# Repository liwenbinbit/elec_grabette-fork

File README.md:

# "Grabette"/"Gripette" Electronic Boards

This repository is part of the ["Grabette" project](https://github.com/pollen-robotics/grabette). It gathers several small PCBs of Grabette/Gripette. 

## Grabette
Grapette is the data acquisition side.

It is based on a battery-powered Raspberry PI 4 plus a [HAT](https://github.com/pollen-robotics/elec_RPI_Robot_HAT) to which a serie of sensing elements is added. Camera, Stereo Camera, angle sensors, IMU (included on the HAT) and a button + a LED as user interface.

 - angle_sensor

 - IMU (Not used)

 - HMI

## Gripette
Gripette is the actuator side. 

It also gathers data with the same Camera/Stereo Camera system and drive motors. The "under-HAT" electronic board is associated to a Raspberry PI zero 2W. It has a interface to the motors (now Feetech wiring). A Bulk-head board makes the mechanical interface with the arm that holds Gripette.

Bulk-head:

## Basically
 - Designed with KiCAD 9.

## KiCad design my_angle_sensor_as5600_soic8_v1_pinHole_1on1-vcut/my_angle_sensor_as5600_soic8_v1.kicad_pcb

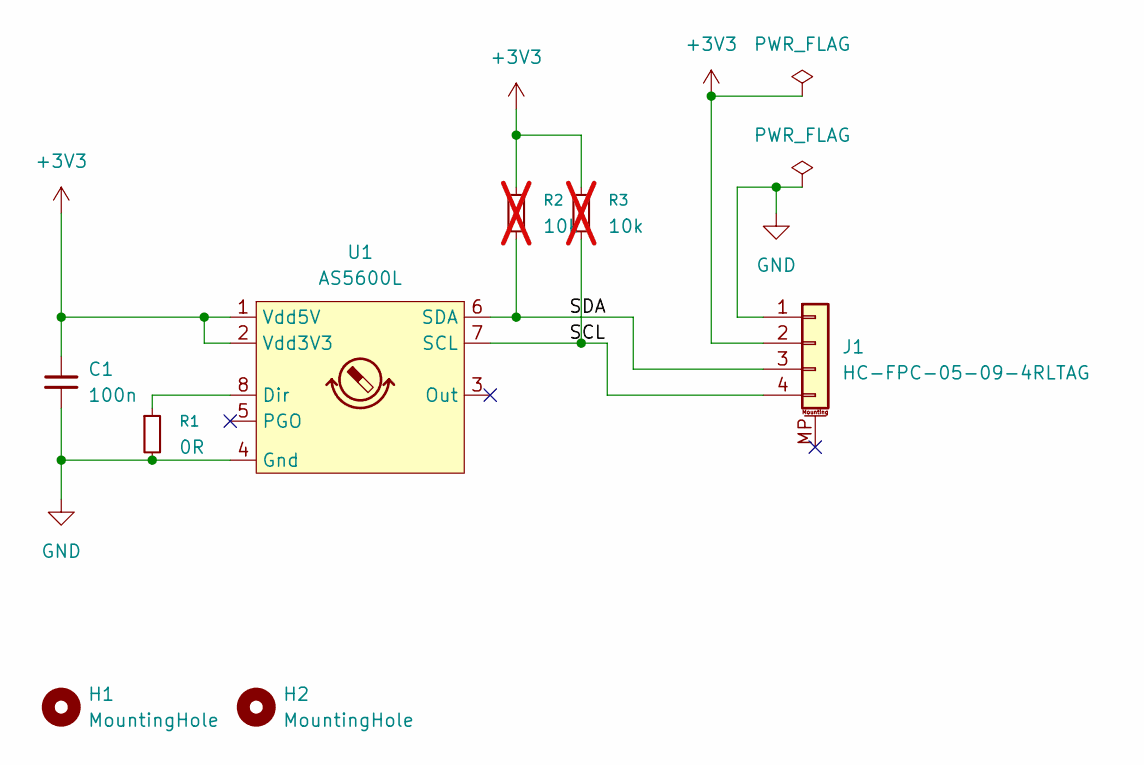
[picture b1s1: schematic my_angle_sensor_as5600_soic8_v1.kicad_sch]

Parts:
C1: 100n; C_0402_1005Metric; LCSC Part C307331
H1, H2: MountingHole; LocatingHole_NPTH_D1.0
J1: HC-FPC-05-09-4RLTAG; FPC-SMD_4P-P0.50_HC-FPC-05-09-4RLTAG; LCSC Part C5213746
R1: 0R; R_0402_1005Metric; LCSC Part C17168
R2, R3: 10k; R_0402_1005Metric; not fitted
U1: AS5600L; SOIC-8_3.9x4.9mm_P1.27mm; LCSC Part C2153666

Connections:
+3V3: C1.1, J1.2, R2.1, R3.1, U1.1 (Vdd5V), U1.2 (Vdd3V3)
/SCL: J1.4, R3.2, U1.7 (SCL)
/SDA: J1.3, R2.2, U1.6 (SDA)
GND: C1.2, J1.1, R1.2, U1.4 (Gnd)
unnamed: R1.1, U1.8 (Dir)

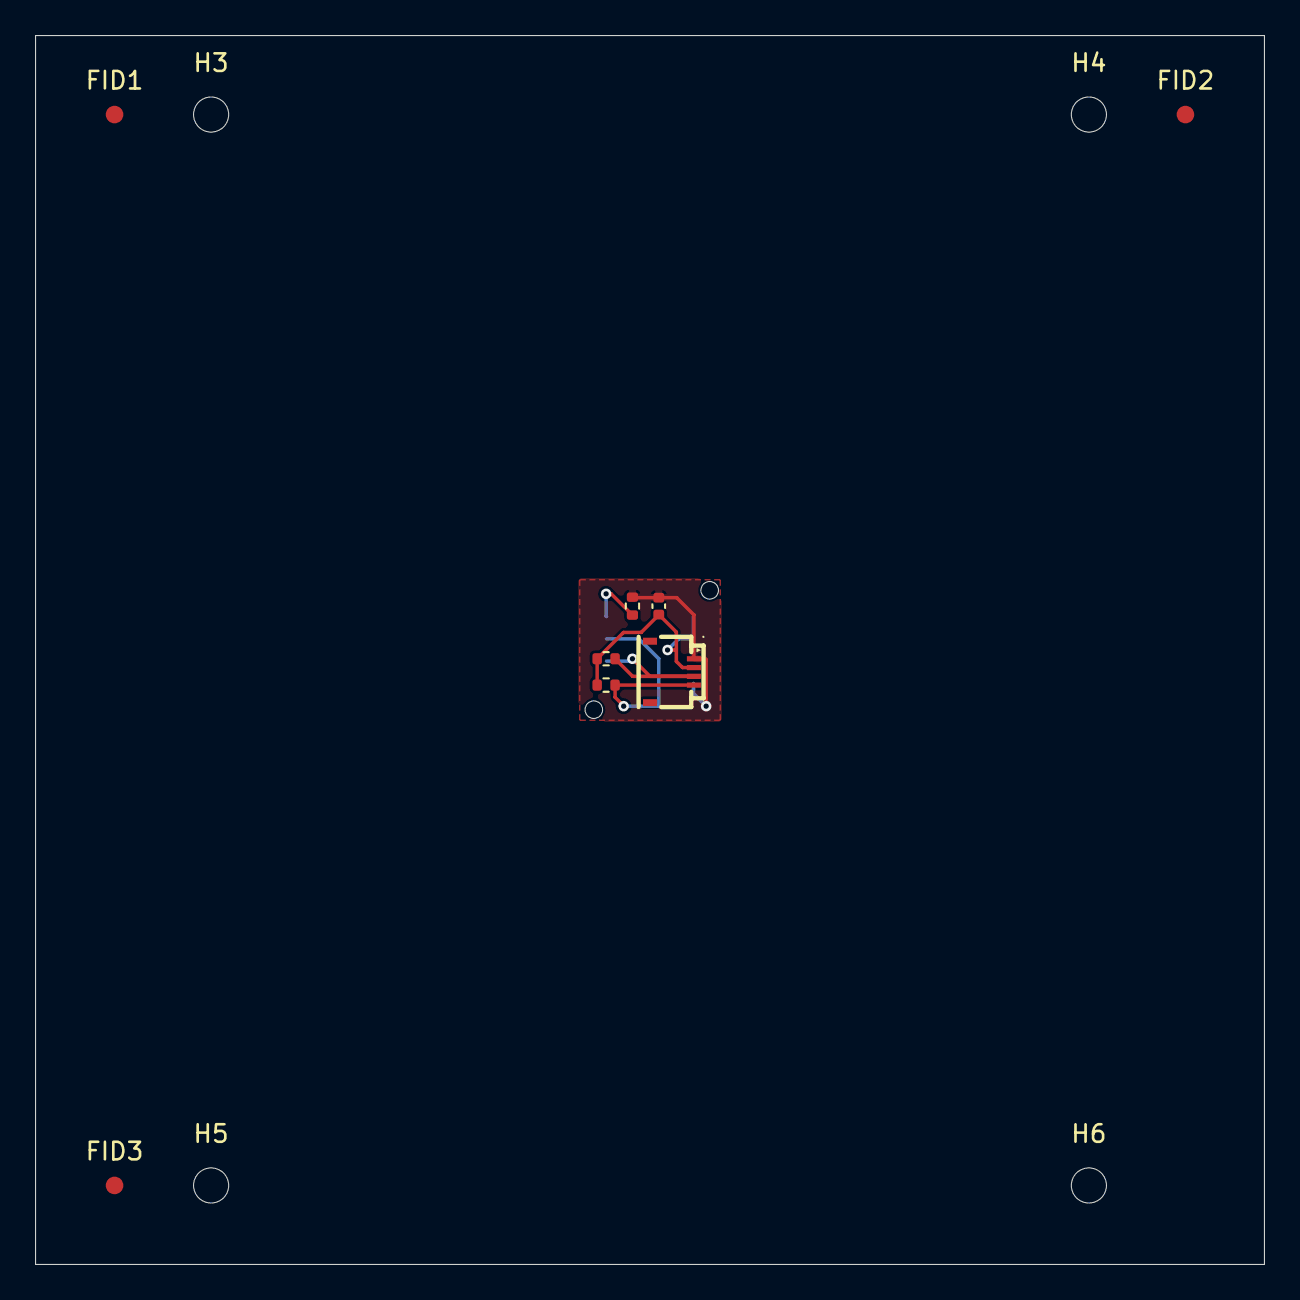
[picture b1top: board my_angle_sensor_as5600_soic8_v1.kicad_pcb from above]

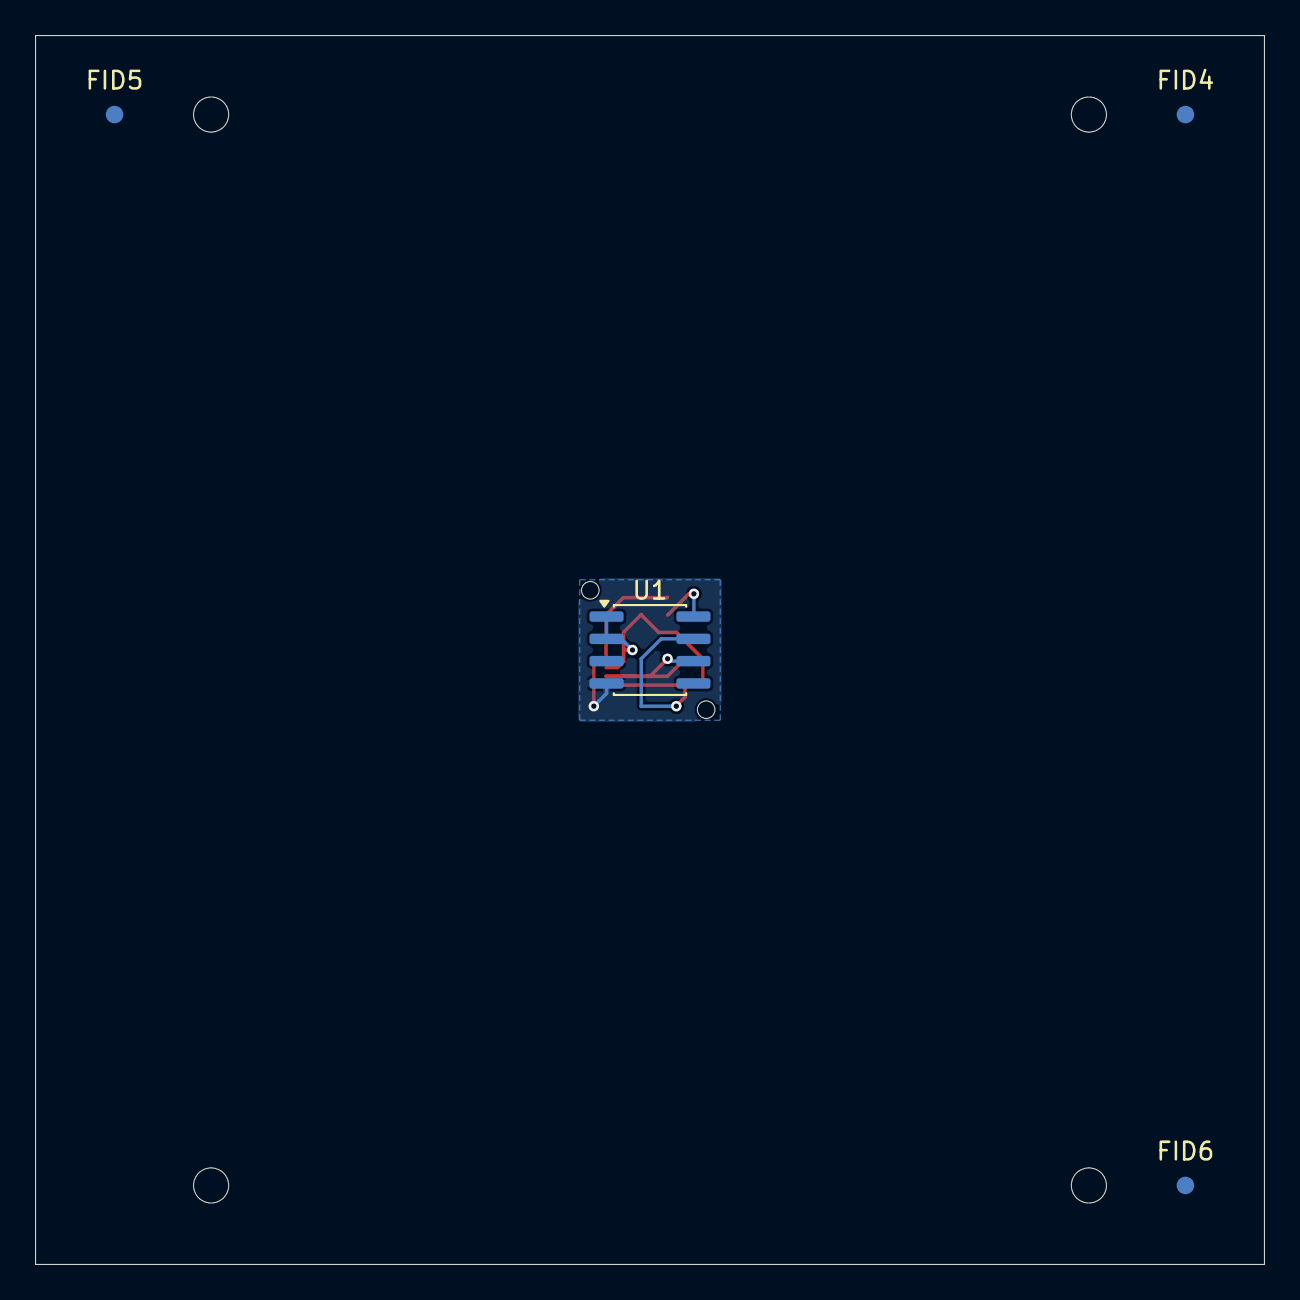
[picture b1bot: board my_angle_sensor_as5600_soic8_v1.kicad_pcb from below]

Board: 2 copper layers, 70.0 x 70.0 mm, 18 parts (4 on the bottom side), 5 nets.

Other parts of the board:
FID1, FID2, FID3, FID4, FID5, FID6: Fiducial_1mm_Mask2mm
H3, H4, H5, H6: MountingHole_2mm

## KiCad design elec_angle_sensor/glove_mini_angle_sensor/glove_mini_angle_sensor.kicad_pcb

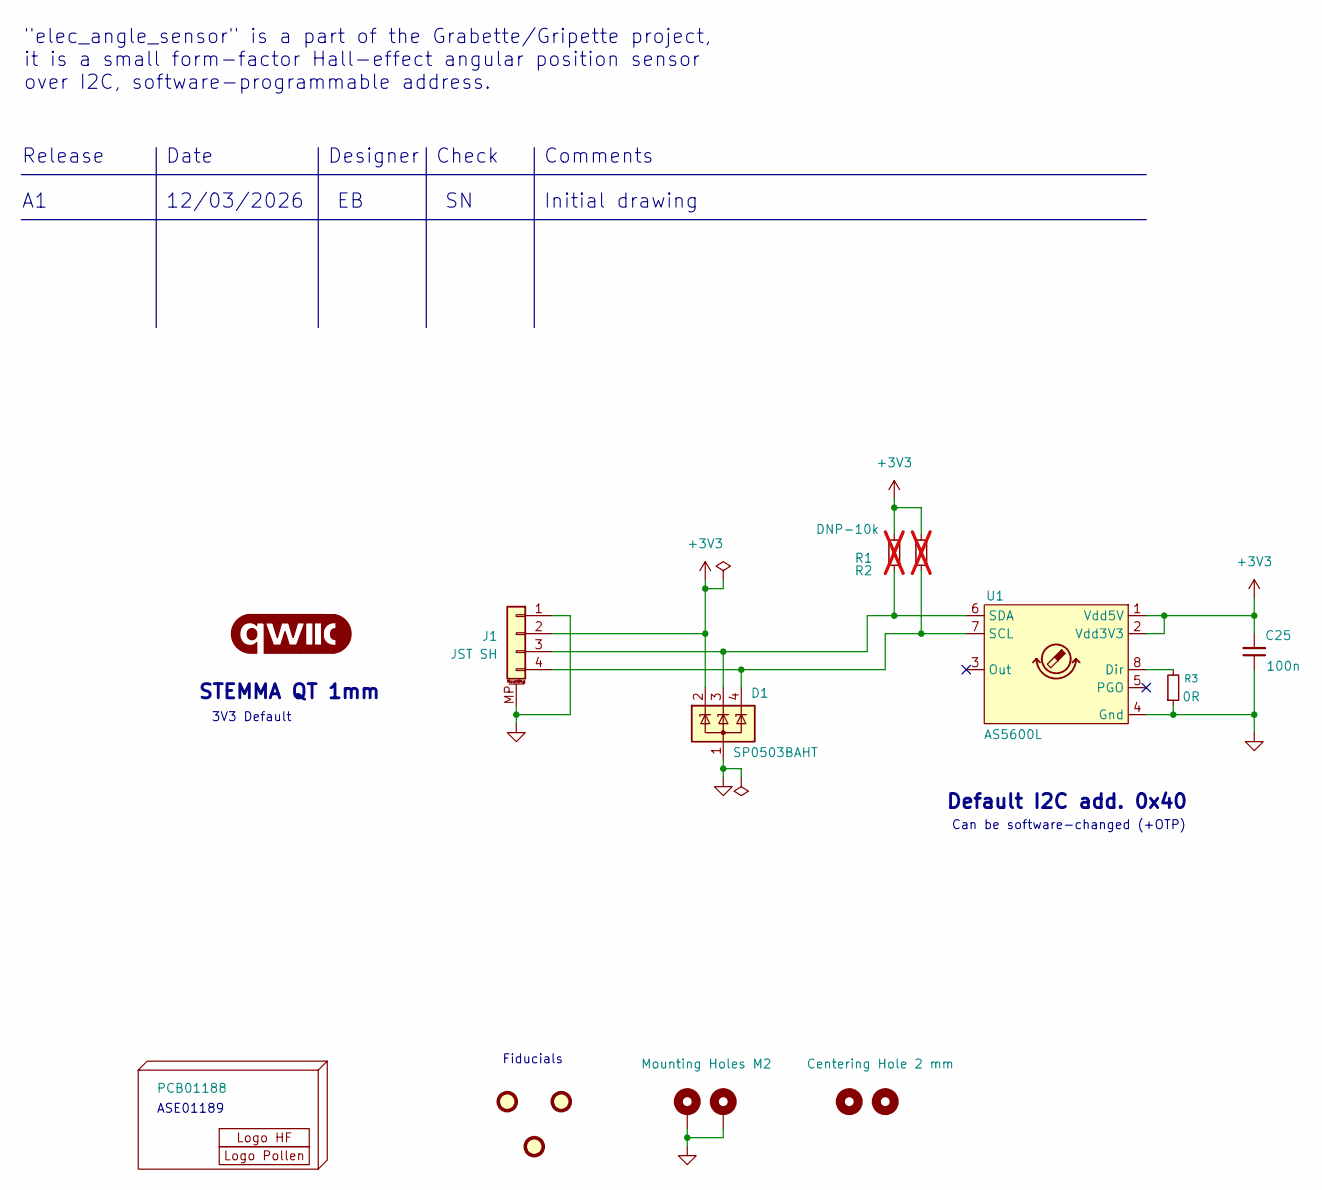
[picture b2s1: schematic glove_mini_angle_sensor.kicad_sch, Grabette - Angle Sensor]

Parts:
C25: 100n; C_0402_1005Metric; LCSC Part C307331
D1: SP0503BAHT; SOT-143; LCSC Part C41364459
FID1, FID2, FID3: DNP Fiducial; Fiducial_1mm_Mask2mm
G1: qwiic_Logo; Logo_qwiic_5mm
H1: PCB01188
H2: Logo HF 2025; Logo_HF_2025
H3: DNP Logo Pollen 2021; Logo_Pollen_2021_sq
H4, H5: Mounting Holes M2; MountingHole_2.2mm_M2_ISO7380_Pad_TopBottom
H6, H7: Centering Hole 2 mm; MountingHole_2.0mm
J1: JST SH; JST_SH_SM04B-SRSS-TB_1x04-1MP_P1.00mm_Horizontal; LCSC Part C160404
R1, R2: DNP-10k; R_0402_1005Metric; LCSC Part C25744; not fitted
R3: 0R; R_0402_1005Metric; LCSC Part C17168
U1: AS5600L; SOIC-8_3.9x4.9mm_P1.27mm; LCSC Part C2153666

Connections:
+3V3: C25.2, D1.2 (K), J1.2, R1.1, R2.1, U1.1 (Vdd5V), U1.2 (Vdd3V3)
GND: C25.1, D1.1 (A), H4.1 (1_1), H5.1 (1_1), J1.1, J1.MP (MountPin), R3.1, U1.4 (Gnd)
unnamed: D1.3 (K), J1.3, R1.2, U1.6 (SDA)
unnamed: D1.4 (K), J1.4, R2.2, U1.7 (SCL)
unnamed: R3.2, U1.8 (Dir)

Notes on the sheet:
Can be software-changed (+OTP)
Date
Check
Release
STEMMA QT 1mm
Fiducials
ASE01189
3V3 Default
Initial drawing
"elec_angle_sensor" is a part of the Grabette/Gripette project, it is a small form-factor Hall-effect angular position sensor over I2C, software-programmable address.
Designer
Default I2C add. 0x40
Comments
12/03/2026

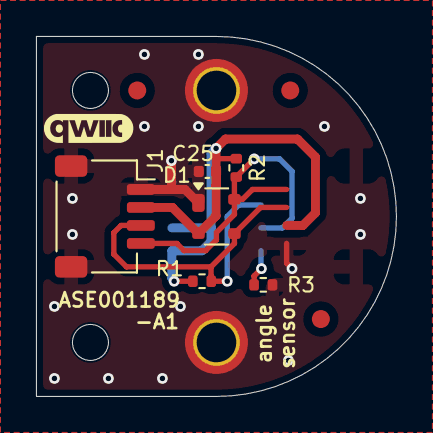
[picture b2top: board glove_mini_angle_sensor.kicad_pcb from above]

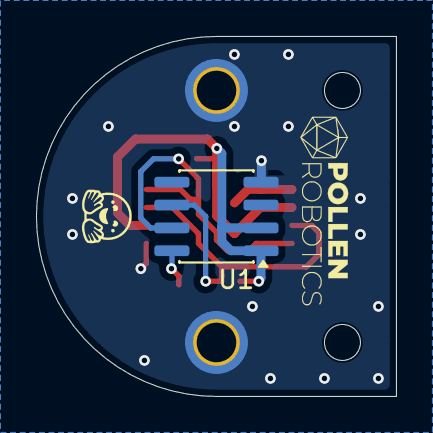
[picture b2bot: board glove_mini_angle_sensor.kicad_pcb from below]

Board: 2 copper layers, 20.0 x 20.0 mm, 17 parts (3 on the bottom side), 5 nets.

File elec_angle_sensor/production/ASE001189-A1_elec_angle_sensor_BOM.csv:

Designator,Footprint,Quantity,Value,LCSC Part #
C25,0402,1,100n,C307331
D1,SOT-143,1,SP0503BAHT,C41364459
G1,Logo_qwiic_5mm,1,qwiic_Logo,
H2,Logo_HF_2025,1,Logo HF 2025,
"J1, J7",JST_SH_SM04B-SRSS-TB_1x04-1MP_P1.00mm_Horizontal,2,JST SH,C160404
"R1, R2",0402,2,DNP-10k,C25744
R3,0402,1,0R,C17168
U1,SOIC-8_3.9x4.9mm_P1.27mm,1,AS5600L,C2153666

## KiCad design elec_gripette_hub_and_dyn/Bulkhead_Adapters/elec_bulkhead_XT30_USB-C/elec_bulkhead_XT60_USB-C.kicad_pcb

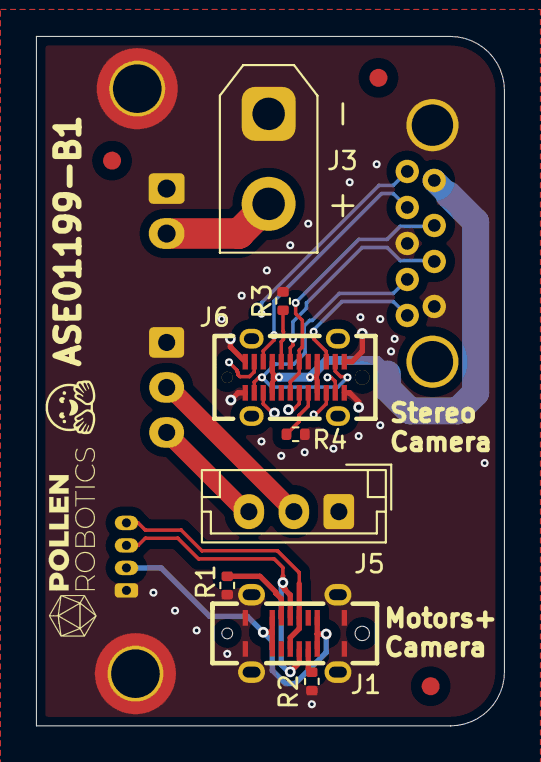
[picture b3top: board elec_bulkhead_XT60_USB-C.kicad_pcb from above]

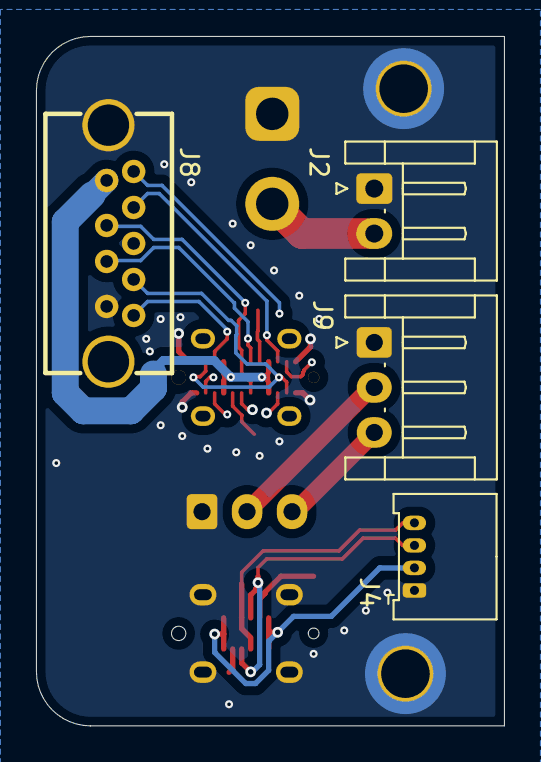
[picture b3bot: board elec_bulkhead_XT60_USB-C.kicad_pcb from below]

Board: 4 copper layers, 26.0 x 38.3 mm, 19 parts (4 on the bottom side), 18 nets.

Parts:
FID1, FID2, FID3: DNP Fiducial; Fiducial_1mm_Mask2mm
H2: Logo HF 2025; Logo_HF_2025
H3: DNP Logo Pollen 2021; Logo_Pollen_2021_sq
H4, H5: Mounting Hole M2,5; MountingHole_2.7mm_M2.5_ISO14580_Pad_TopBottom
J1: USB-C Rec. Vert.; USB-C_16p_vert_Shou-Han_TYPE-C 16P LTH6.8 - C5187468
J2: JST EH 2; JST_EH_S2B-EH_1x02_P2.50mm_Horizontal
J3: XT30; AMASS_XT30UPB-M_1x02_P5.0mm_Vertical
J4: pico4; Molex_PicoBlade_53048-0410_1x04_P1.25mm_Horizontal
J5: DNP - Dynamixel-3; JST_EH_B3B-EH-A_1x03_P2.50mm_Vertical
J6: USB_C_Receptacle; USB-C_TYPE-C-24PLT-H10.5-1
J8: USB3_A; USB-A-TH_MOLEX_484080003
J9: DNP - Dynamixel-3; JST_EH_S3B-EH_1x03_P2.50mm_Horizontal
R1, R2, R3, R4: 5k1; R_0402_1005Metric

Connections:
+BATT: J2.2, J3.2
/D+: J6.A6 (D+), J6.B6 (D+), J8.3 (D+)
/D-: J6.A7 (D-), J6.B7 (D-), J8.2 (D-)
/DM+: J1.A6 (D+), J1.B6 (D+), J4.3
/DM-: J1.A7 (D-), J1.B7 (D-), J4.4
/SSRx+: J6.A11 (RX2+), J6.B11 (RX1+), J8.6 (SSRX+)
/SSRx-: J6.A10 (RX2-), J6.B10 (RX1-), J8.5 (SSRX-)
/SSTx+: J6.A2 (TX1+), J6.B2 (TX2+), J8.9 (SSTX+)
/SSTx-: J6.A3 (TX1-), J6.B3 (TX2-), J8.8 (SSTX-)
GND: H4.1, H5.1, J1.A1 (GND), J1.A12 (GND), J1.B1 (GND), J1.B12 (GND), J1.S1 (SHIELD), J2.1, J3.1, J4.1, J5.1, J6.A1 (GND), J6.A12 (GND), J6.B1 (GND), J6.B12 (GND), J8.4 (GND), J8.7 (DRAIN), J8.10 (SHIELD), J9.1, R1.2, R2.2, R3.2, R4.2
unnamed: J1.A5 (CC1), R1.1
unnamed: J1.B5 (CC2), R2.1
unnamed: J1.A4 (VBUS), J1.A9 (VBUS), J1.B4 (VBUS), J1.B9 (VBUS), J4.2
unnamed: J5.2, J9.2
unnamed: J5.3, J9.3
unnamed: J6.A5 (CC1), R3.1
unnamed: J6.B5 (CC2), R4.1
unnamed: J6.A4 (VBUS), J6.A9 (VBUS), J6.B4 (VBUS), J6.B9 (VBUS), J8.1 (VBUS)

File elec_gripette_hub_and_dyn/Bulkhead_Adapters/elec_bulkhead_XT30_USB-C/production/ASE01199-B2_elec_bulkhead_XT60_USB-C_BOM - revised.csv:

Designator,Footprint,Quantity,Value,LCSC Part #
,,,,
J1,USB-C_16p_vert_Shou-Han_TYPE-C 16P LTH6.8 - C5187468,1,USB-C Rec. Vert.,C5187468
J2,JST_EH_S2B-EH_1x02_P2.50mm_Horizontal,1,JST EH 2,C514173
J3,AMASS_XT30UPB-M_1x02_P5.0mm_Vertical,1,XT30,C428721
J4,Molex_PicoBlade_53048-0410_1x04_P1.25mm_Horizontal,1,pico4,C588275
,,,,
J6,USB-C_TYPE-C-24PLT-H10.5-1,1,USB_C_Receptacle,C3151750
J8,USB-A-TH_MOLEX_484080003,1,USB3_A,C587839
,,,,
"R1, R2, R3, R4",0402,4,5k1,C25905

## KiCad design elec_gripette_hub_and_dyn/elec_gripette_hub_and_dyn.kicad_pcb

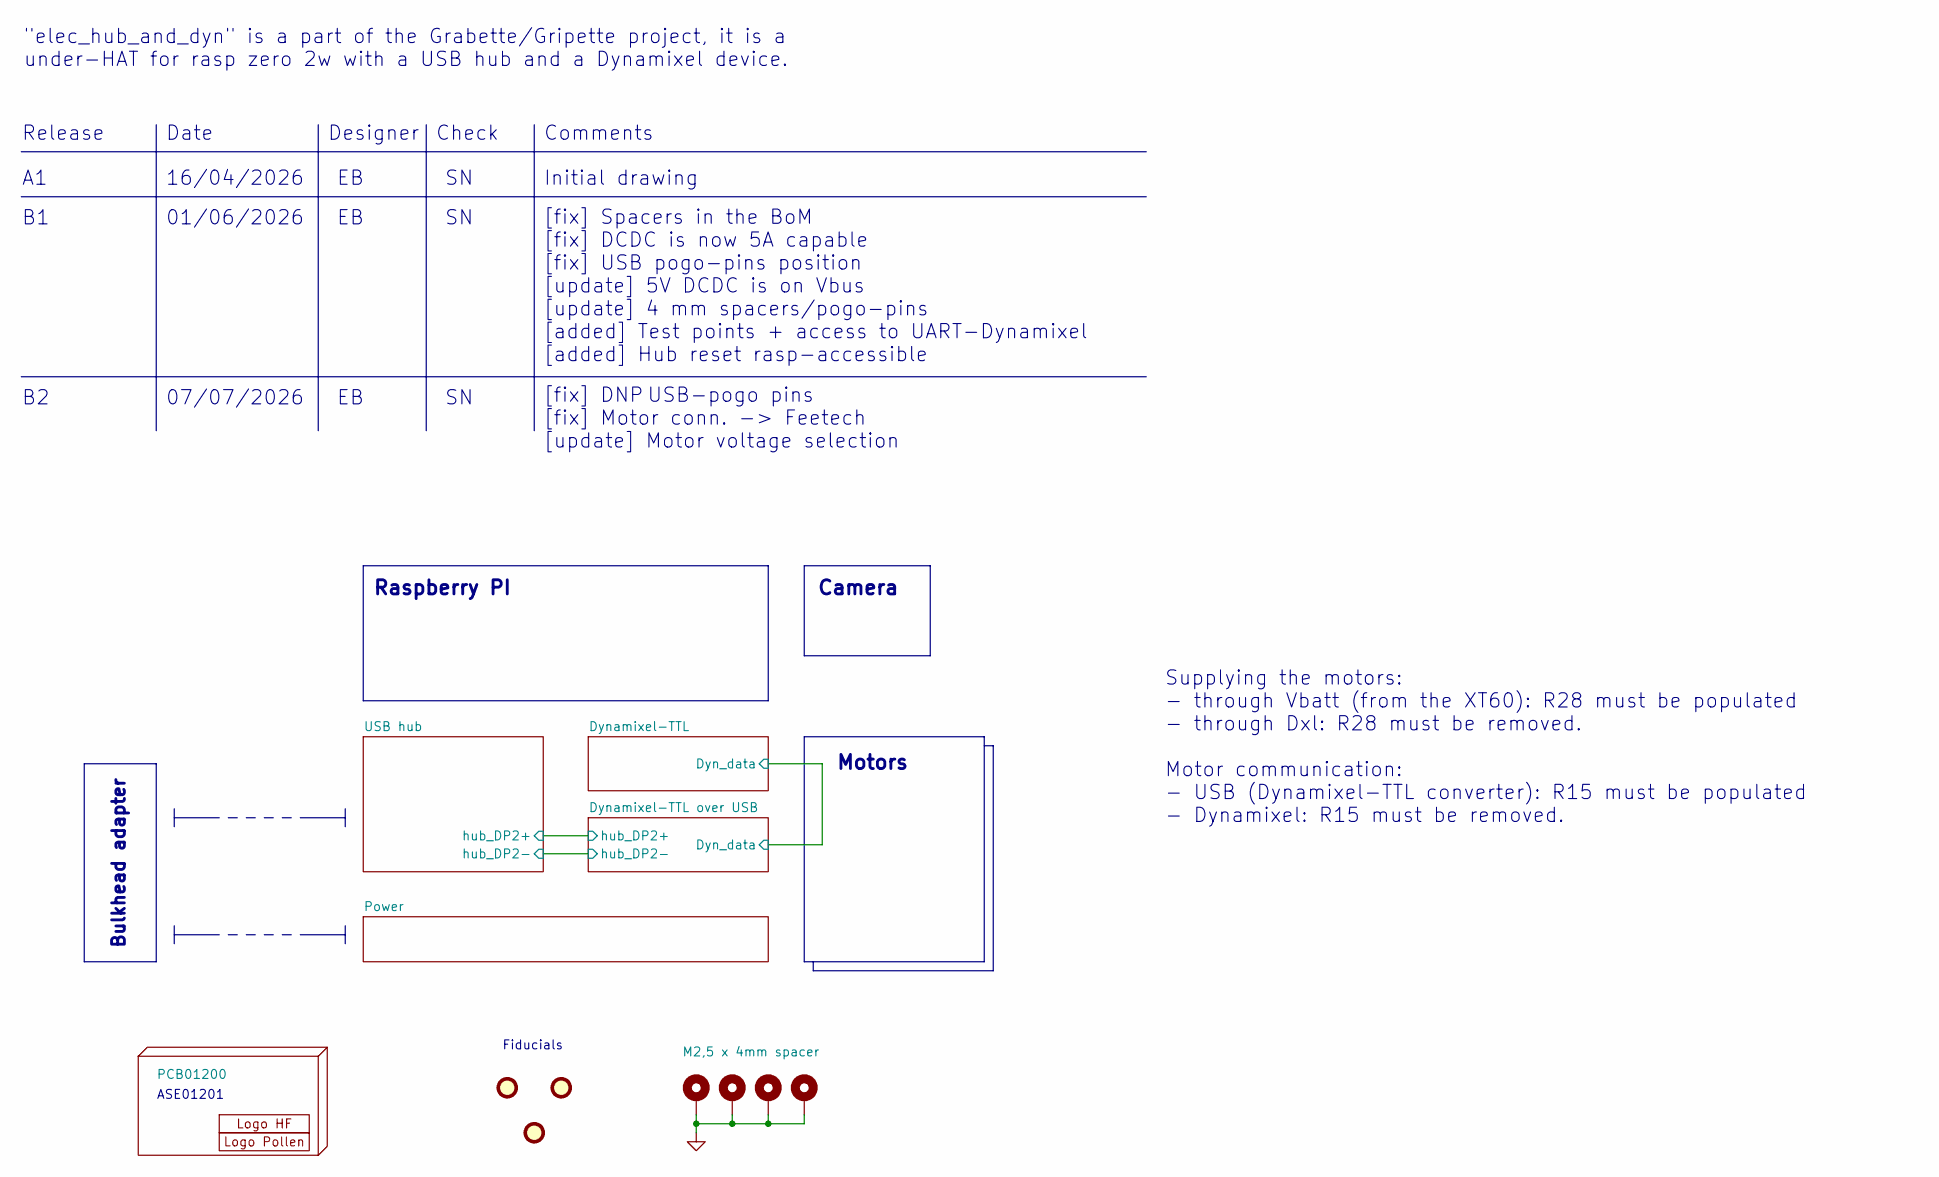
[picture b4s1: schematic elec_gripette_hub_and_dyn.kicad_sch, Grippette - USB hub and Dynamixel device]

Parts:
FID1, FID2, FID3: DNP Fiducial; Fiducial_1mm_Mask2mm
H1: PCB01200
H2: Logo HF 2025; Logo_HF_2025
H3: DNP Logo Pollen 2021; Logo_Pollen_2021_sq
H4, H5, H6, H7: M2,5 x 4mm spacer; SMD_BD5.6-D4.1_spacer; LCSC Part C2916324

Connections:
GND: H4.1, H5.1, H6.1, H7.1; also elsewhere on the board

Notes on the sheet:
Date
[fix] Spacers in the BoM [fix] DCDC is now 5A capable [fix] USB pogo-pins position [update] 5V DCDC is on Vbus [update] 4 mm spacers/pogo-pins [added] Test points + access to UART-Dynamixel [added] Hub reset rasp-accessible
Check
Release
Fiducials
ASE01201
Motors
Supplying the motors: - through Vbatt (from the XT60): R28 must be populated - through Dxl: R28 must be removed. Motor communication: - USB (Dynamixel-TTL converter): R15 must be populated - Dynamixel: R15 must be removed.
Raspberry PI
Camera
Initial drawing
"elec_hub_and_dyn" is a part of the Grabette/Gripette project, it is a under-HAT for rasp zero 2w with a USB hub and a Dynamixel device.
Designer
[fix] DNP USB-pogo pins [fix] Motor conn. -> Feetech [update] Motor voltage selection
Bulkhead adapter
07/07/2026
01/06/2026
Comments
16/04/2026

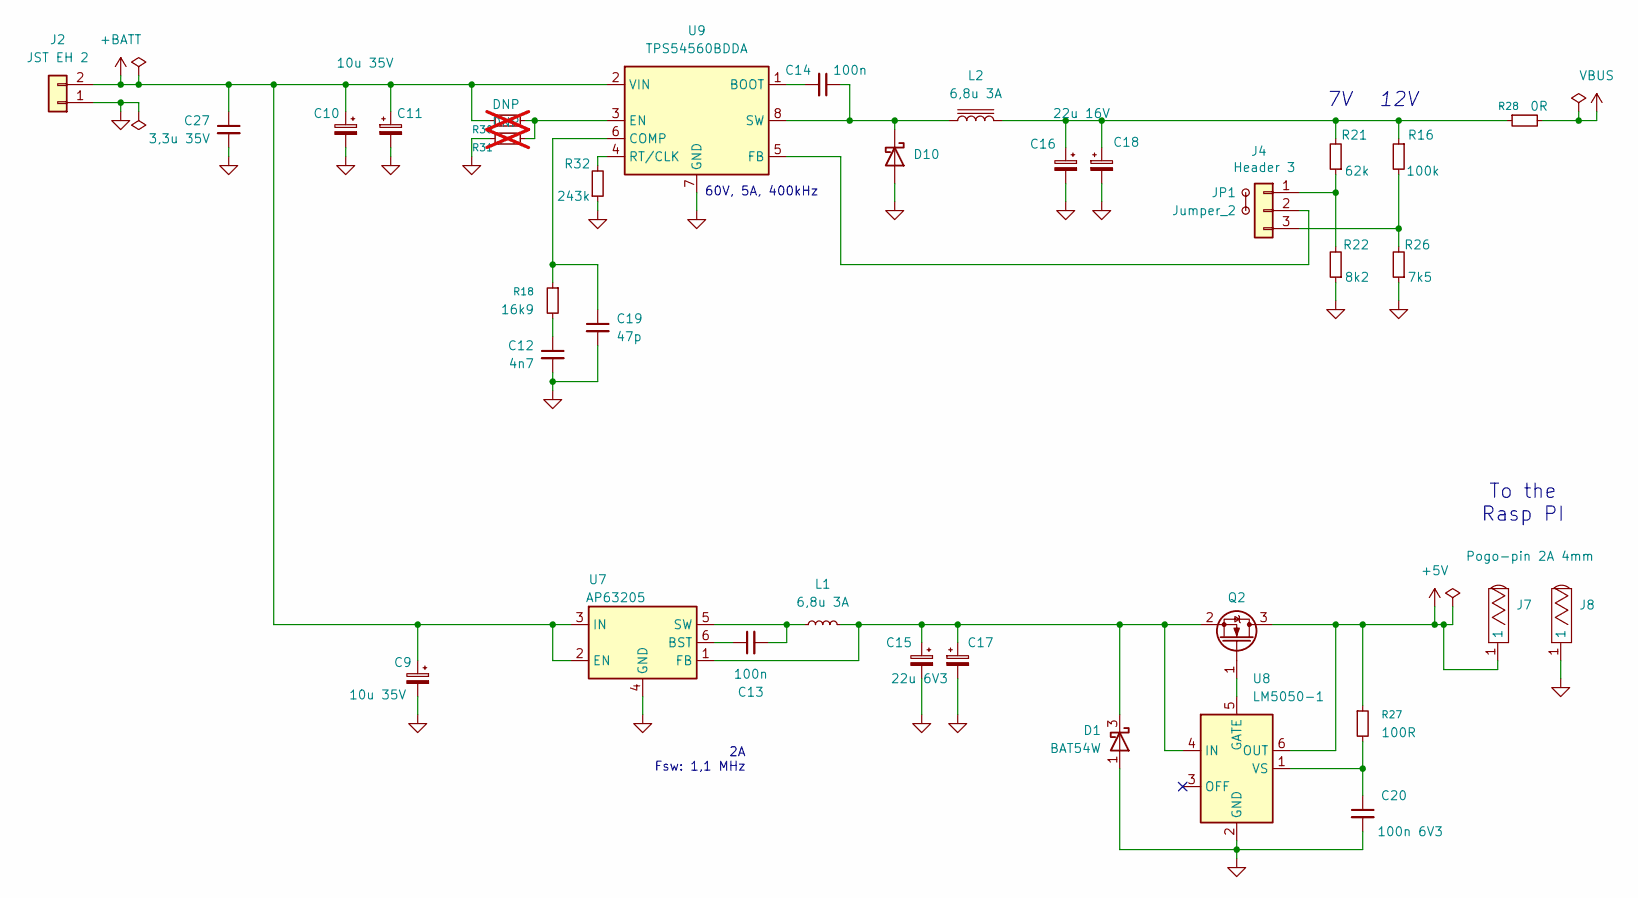
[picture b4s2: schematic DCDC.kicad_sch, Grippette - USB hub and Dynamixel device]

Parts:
C9, C10, C11: 10u 35V; CP_Elec_6.3x7.7; LCSC Part C72488
C12: 4n7; C_0402_1005Metric; LCSC Part C1518204
C13, C14: 100n; C_0402_1005Metric; LCSC Part C307331
C15, C17: 22u 6V3; C_0603_1608Metric; LCSC Part C84419
C16, C18: 22u 16V; CP_Elec_4x5.4; LCSC Part C72502
C19: 47p; C_0402_1005Metric; LCSC Part C1567
C20: 100n 6V3; C_0402_1005Metric; LCSC Part C1525
C27: 3,3u 35V; C_0805_2012Metric; LCSC Part C361184
D1: BAT54W; SOT-323_SC-70; LCSC Part C78606
D10: D_Schottky 3A; D_SMA; LCSC Part C8678
J2: JST EH 2; JST_EH_B2B-EH-A_1x02_P2.50mm_Vertical; LCSC Part C160262
J4: Header 3; PinHeader_1x03_P1.27mm_Vertical; LCSC Part C7470079
J7, J8: Pogo-pin 2A 4mm; CONN-TH_YZ08415060P-02_pogo; LCSC Part C7471674
JP1: Jumper_2; LCSC Part C150949
L1, L2: 6,8u 3A; L_Bourns_SRN6045TA; LCSC Part C57254
Q2: SI2312CDS-T1-GE3; TSOT-23; LCSC Part C142518
R16: 100k; R_0402_1005Metric; LCSC Part C2906883
R18: 16k9; R_0402_1005Metric; LCSC Part C25858
R21: 62k; R_0402_1005Metric; LCSC Part C2909375
R22: 8k2; R_0402_1005Metric; LCSC Part C25924
R26: 7k5; R_0402_1005Metric; LCSC Part C25918
R27: 100R; R_0402_1005Metric; LCSC Part C2906860
R28: 0R; R_0603_1608Metric; LCSC Part C21189
R30, R31: DNP; R_0402_1005Metric; not fitted
R32: 243k; R_0402_1005Metric; LCSC Part C43249
U7: AP63205; TSOT-23-6; LCSC Part C2071056
U8: LM5050-1; TSOT-23-6; LCSC Part C473393
U9: TPS54560BDDA; Texas_R-PDSO-G8_EP2.95x4.9mm_Mask2.4x3.1mm_ThermalVias; LCSC Part C1850354

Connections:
+5V: J7.1, Q2.3 (D), R27.1, U8.6 (OUT); also elsewhere on the board
+BATT: C9.1, C10.1, C11.1, C27.1, J2.2, R30.1, U7.2 (EN), U7.3 (IN), U9.2 (VIN)
GND: C9.2, C10.2, C11.2, C12.2, C15.2, C16.2, C17.2, C18.2, C19.2, C20.2, C27.2, D1.1 (A), D10.2 (A), J2.1, J8.1, R22.1, R26.1, R31.1, R32.1, U7.4 (GND), U8.2 (GND), U9.7 (GND), U9.9 (GND); also elsewhere on the board
unnamed: C12.1, R18.2
unnamed: C16.1, C18.1, L2.1, R16.1, R21.2, R28.1
unnamed: C15.1, C17.1, D1.3 (K), L1.1, Q2.2 (S), U7.1 (FB), U8.4 (IN)
unnamed: C14.1, D10.1 (K), L2.2, U9.8 (SW)
unnamed: J4.1, R21.1, R22.2
unnamed: J4.2, U9.5 (FB)
unnamed: J4.3, R16.2, R26.2
unnamed: Q2.1 (G), U8.5 (GATE)
unnamed: C13.1, U7.6 (BST)
unnamed: C13.2, L1.2, U7.5 (SW)
unnamed: C20.1, R27.2, U8.1 (VS)
unnamed: C14.2, U9.1 (BOOT)
unnamed: C19.1, R18.1, U9.6 (COMP)
unnamed: R30.2, R31.2, U9.3 (EN)
unnamed: R32.2, U9.4 (RT/CLK)
VBUS: R28.2; also elsewhere on the board

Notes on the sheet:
60V, 5A, 400kHz
2A Fsw: 1,1 MHz
To the Rasp PI
12V

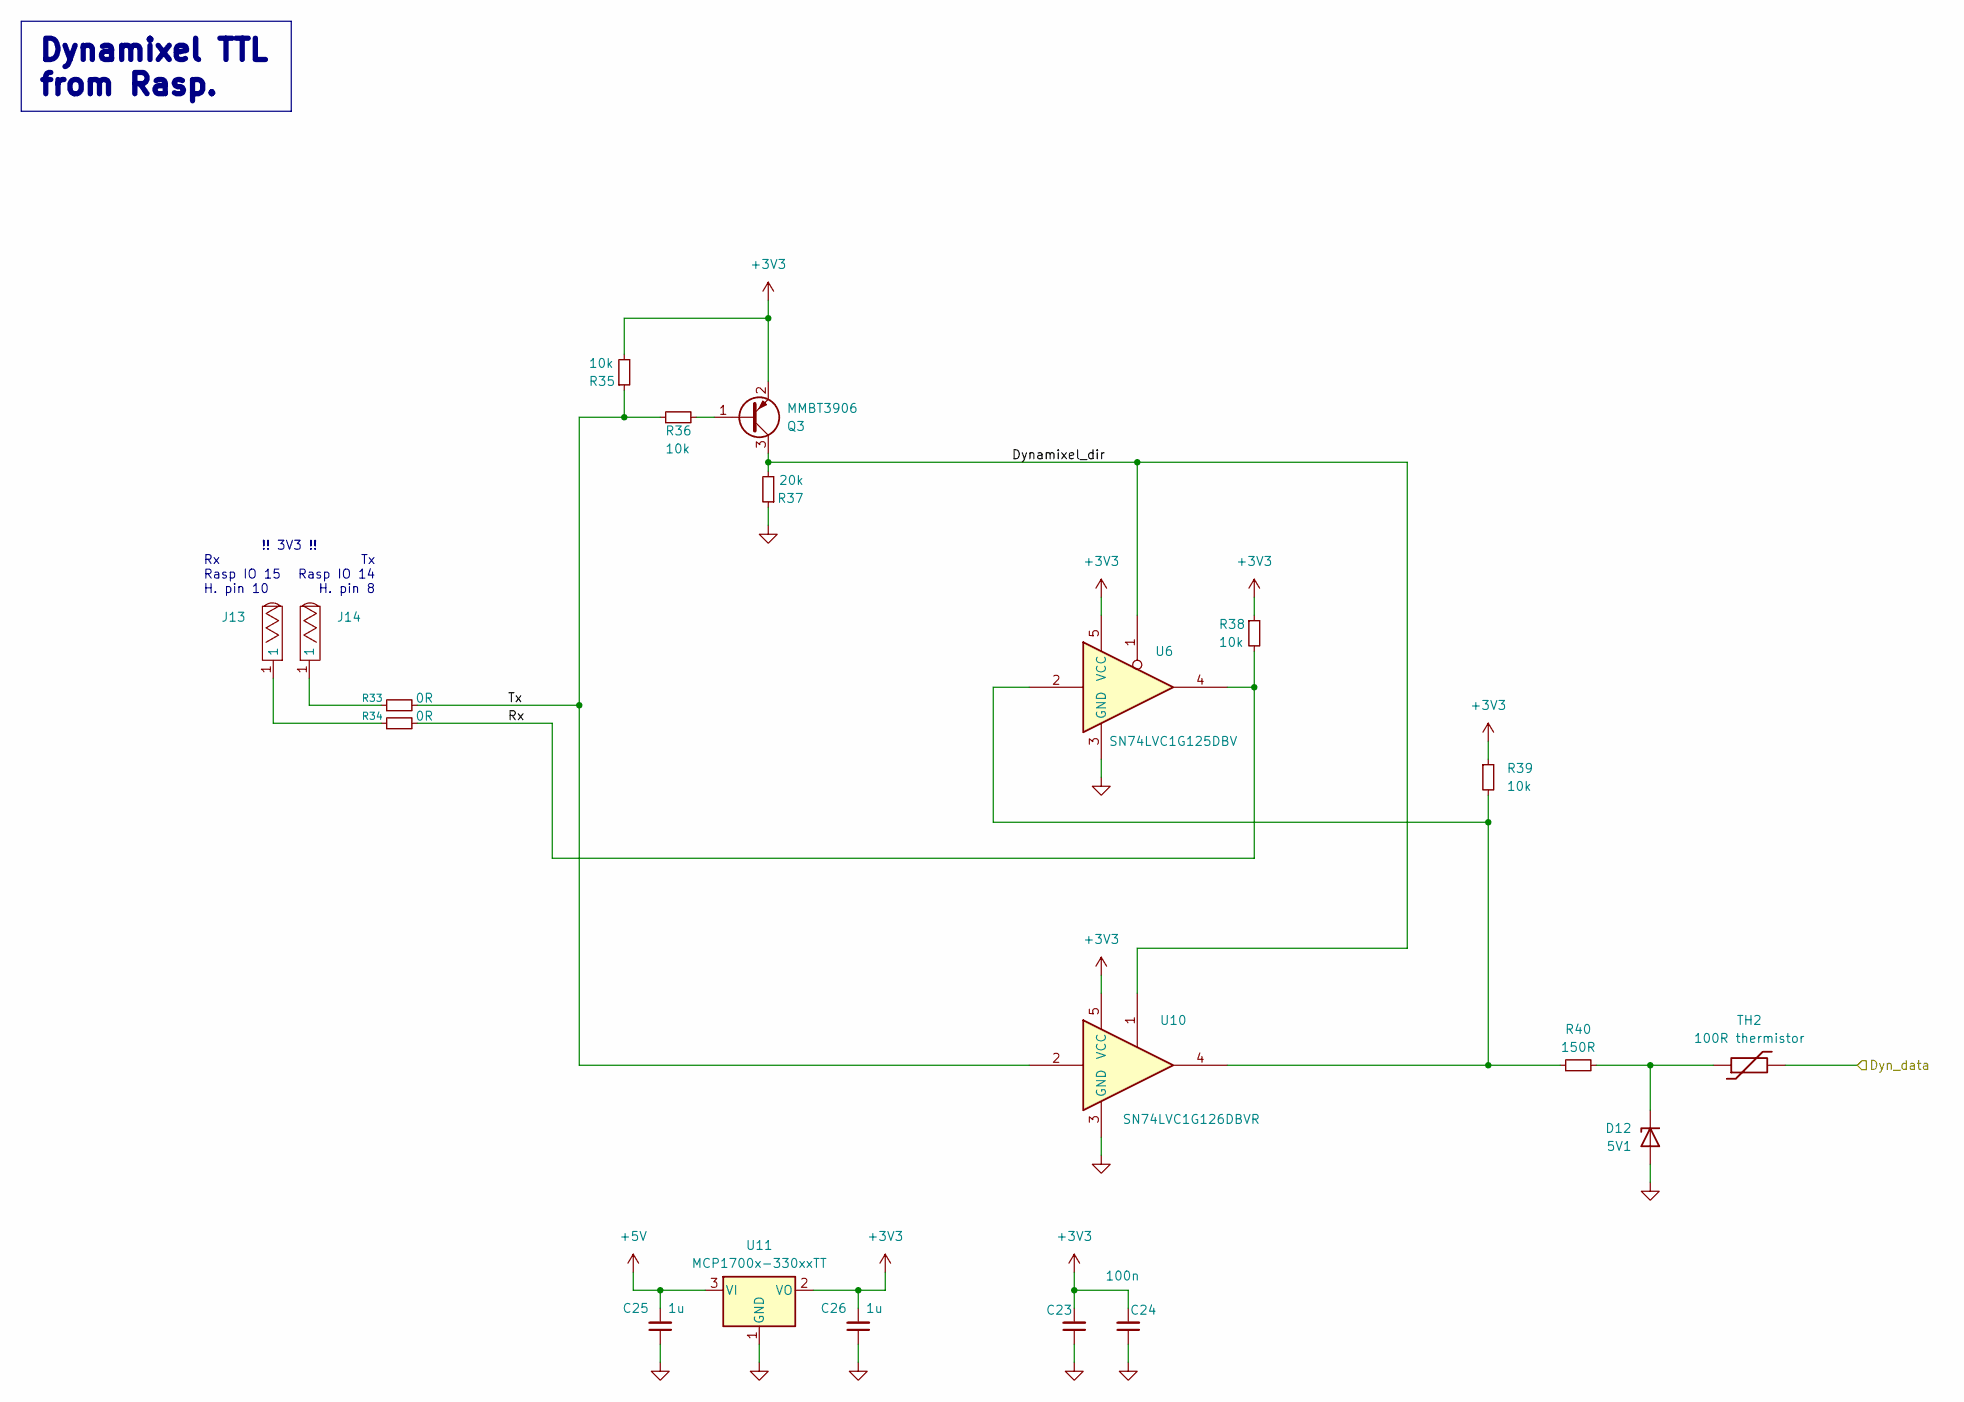
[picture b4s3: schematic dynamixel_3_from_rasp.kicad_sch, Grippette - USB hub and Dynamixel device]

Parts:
C23, C24: 100n; C_0603_1608Metric; LCSC Part C85864
C25, C26: 1u; C_0603_1608Metric; LCSC Part C1592
D12: 5V1; D_SOD-323; LCSC Part C151348
J13, J14: Pogo-pin 4mm; CONN-TH_YZ95315064P-01_pogo; LCSC Part C5157245
Q3: MMBT3906; SOT-23; LCSC Part C727128
R33, R34: 0R; R_0402_1005Metric; LCSC Part C17168
R35, R36, R38, R39: 10k; R_0402_1005Metric; LCSC Part C25744
R37: 20k; R_0402_1005Metric; LCSC Part C2906867
R40: 150R; R_0402_1005Metric; LCSC Part C138054
TH2: 100R thermistor; R_0603_1608Metric; LCSC Part C913703
U6: SN74LVC1G125DBV; SOT-23-5; LCSC Part C23654
U10: SN74LVC1G126DBVR; SOT-23-5; LCSC Part C7834
U11: MCP1700x-330xxTT; SOT-23; LCSC Part C39051

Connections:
+3V3: C23.2, C24.2, C26.2, Q3.2 (E), R35.2, R38.1, R39.1, U6.5 (VCC), U10.5 (VCC), U11.2 (VO)
+5V: C25.2, U11.3 (VI); also elsewhere on the board
/Dynamixel-TTL over USB/Dyn_data: TH2.2; also elsewhere on the board
/Dynamixel-TTL/Dynamixel_dir: Q3.3 (C), R37.2, U6.1, U10.1
/Dynamixel-TTL/Rx: R34.2, R38.2, U6.4
/Dynamixel-TTL/Tx: R33.2, R35.1, R36.1, U10.2
GND: C23.1, C24.1, C25.1, C26.1, D12.2 (A), R37.1, U6.3 (GND), U10.3 (GND), U11.1 (GND); also elsewhere on the board
unnamed: D12.1 (K), R40.2, TH2.1
unnamed: J13.1, R34.1
unnamed: J14.1, R33.1
unnamed: Q3.1 (B), R36.2
unnamed: R39.2, R40.1, U6.2, U10.4

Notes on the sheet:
Tx Rasp IO 14 H. pin 8
Rx Rasp IO 15 H. pin 10
!! 3V3 !!
Dynamixel TTL from Rasp.
